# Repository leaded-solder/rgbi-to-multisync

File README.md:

# NEC MultiSync MDA/CGA/EGA/Japanese DIN RGBI adapter
This adapter is meant to help support multiple old computers when used with the NEC MultiSync line of CRTs.

It has only been tested on the MultiSync 3D. Earlier models may require a different adapter; please check your service manual.

# Current Status
**NOT WORKING** - the MultiSync does not wake up under Japanese RGBI input from either a PC-6601SR or PC-9801UV2.

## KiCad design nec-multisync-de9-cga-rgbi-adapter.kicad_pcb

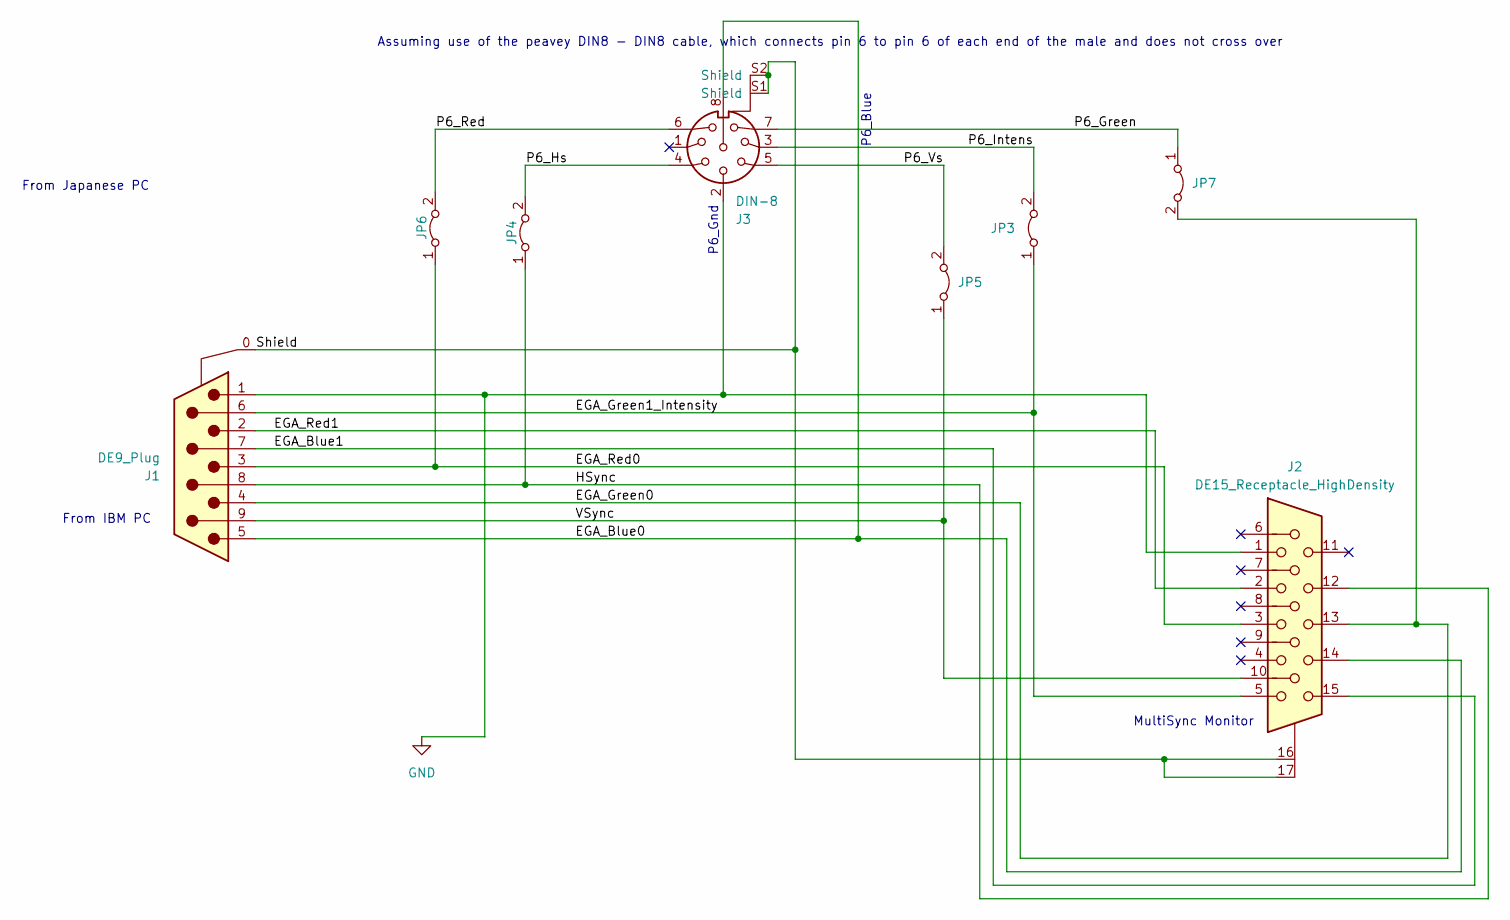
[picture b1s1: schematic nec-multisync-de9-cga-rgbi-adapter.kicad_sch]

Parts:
J1: DE9_Plug; DSUB-9_Male_Horizontal_P2.77x2.84mm_EdgePinOffset7.70mm_Hou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
J2: DE15_Receptacle_HighDensity; FIXED-1-1734530-1
J3: DIN-8; CUI_SDS-80J
JP3, JP4, JP5, JP6, JP7: Jumper_2_Bridged; SolderJumper-2_P1.3mm_Bridged_Pad1.0x1.5mm

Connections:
/EGA_Blue0: J1.5, J2.14, J3.8
/EGA_Blue1: J1.7, J2.15
/EGA_Green0: J1.4, J2.13, JP7.2 (B)
/EGA_Green1_Intensity: J1.6, J2.5, JP3.1 (A)
/EGA_Red0: J1.3, J2.3, JP6.1 (A)
/EGA_Red1: J1.2, J2.2
/HSync: J1.8, J2.12, JP4.1 (A)
/P6_Green: J3.7, JP7.1 (A)
/P6_Hs: J3.4, JP4.2 (B)
/P6_Intens: J3.3, JP3.2 (B)
/P6_Red: J3.6, JP6.2 (B)
/P6_Vs: J3.5, JP5.2 (B)
/Shield: J1.0 (Shield), J2.16 (Shield), J2.17 (Shield), J3.S1 (Shield), J3.S2 (Shield)
/VSync: J1.9, J2.10, JP5.1 (A)
GND: J1.1, J2.1, J3.2

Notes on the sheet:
MultiSync Monitor
P6_Blue
P6_Gnd
From Japanese PC
Assuming use of the peavey DIN8 - DIN8 cable, which connects pin 6 to pin 6 of each end of the male and does not cross over
From IBM PC

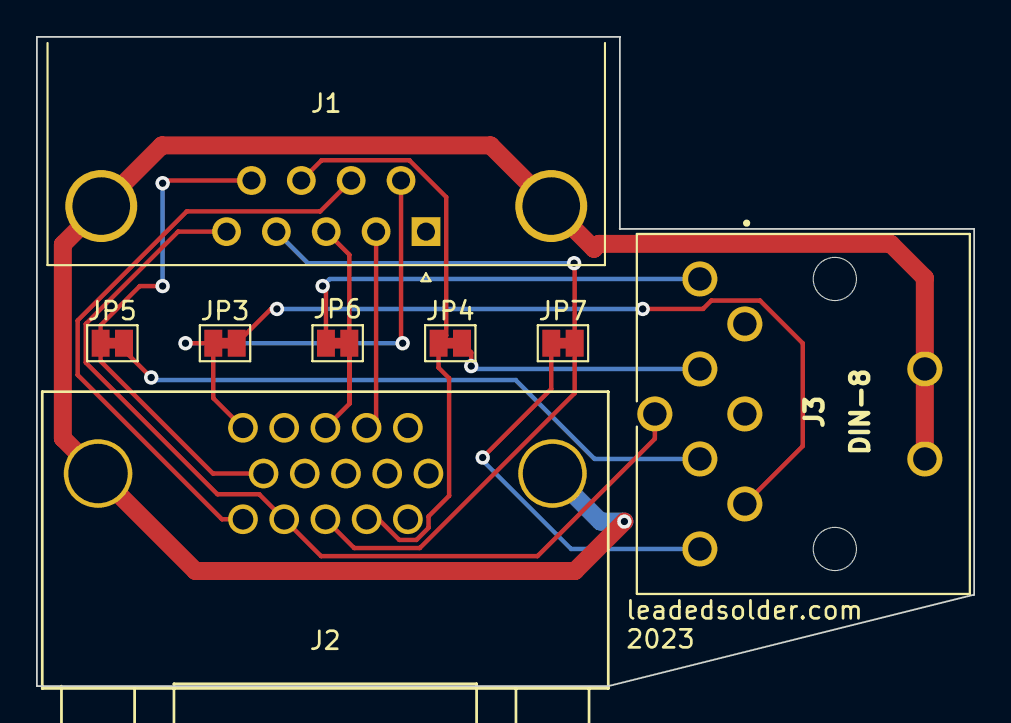
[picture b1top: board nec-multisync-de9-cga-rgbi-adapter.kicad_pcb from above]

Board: 2 copper layers, 52.1 x 36.1 mm, 8 parts (0 on the bottom side), 15 nets.

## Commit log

2023-11-27 initial commit, starting out
2023-11-27 V1 to Fab
2023-12-17 Remove annoying tab that fouls on Tandy
2023-12-17 Update to NOTWORKING
2023-12-18 Artistic label placement
2023-12-18 Maybe reverse my bonehead fuckup of feeding 12V to the MultiSync's signal input
2023-12-18 Label nets
2023-12-18 Prepare to flip DIN
2023-12-18 World's ugliest reroute
2023-12-18 Tie shield pins to ground
2023-12-18 V2 (flipped, DE9 interference fixed) sent to fab
2024-03-28 Tie shields together

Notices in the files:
parts and their libraries:
Copyright 2016 Accelerated Designs. All rights reserved.
